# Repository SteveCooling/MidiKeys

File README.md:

# MidiKeys

Dissecting an old broken organ I got the idea to turn it into a MIDI keyboard.

I've since gotten a keybed that already had dual key switches for the velocity sensitivity, and been working on circuitry and code to support velocity sensitivity.

My plan is to produce a versatile open source keyboard controller board that can be used in various keyboard projects.

Works:

* Velocity sensitive multiplexed keyboard scanning
* Note off velocity sensitivity (not common in commercial keyboards, fun to be had here)

Plans:

* Work out the bugs in the keyboard scanner (keys sometimes hang or go undetected)
* Pot/slider (analog input) multiplexing
* Dedicated PCB with all required components and connectors
* Aftertouch support (channel pressure)
  * Maybe pseudo-polyphonic aftertouch is possible using a handful of pressure sensors (one per octave?) and interpolating the key pressure. Not sure about this.

Maybe in time:

* Mackie style DAW control support
* Keyboard splits and layers
* Interactive configuration from computer
* Arpeggiator with some cool touches?
  * Internal or MIDI timing
  * Oneshot/lick mode: Only arpeggiate when multiple keys are on, and in play order. Lay a chord and let the keyboard "slide" through the notes for you. In tempo.

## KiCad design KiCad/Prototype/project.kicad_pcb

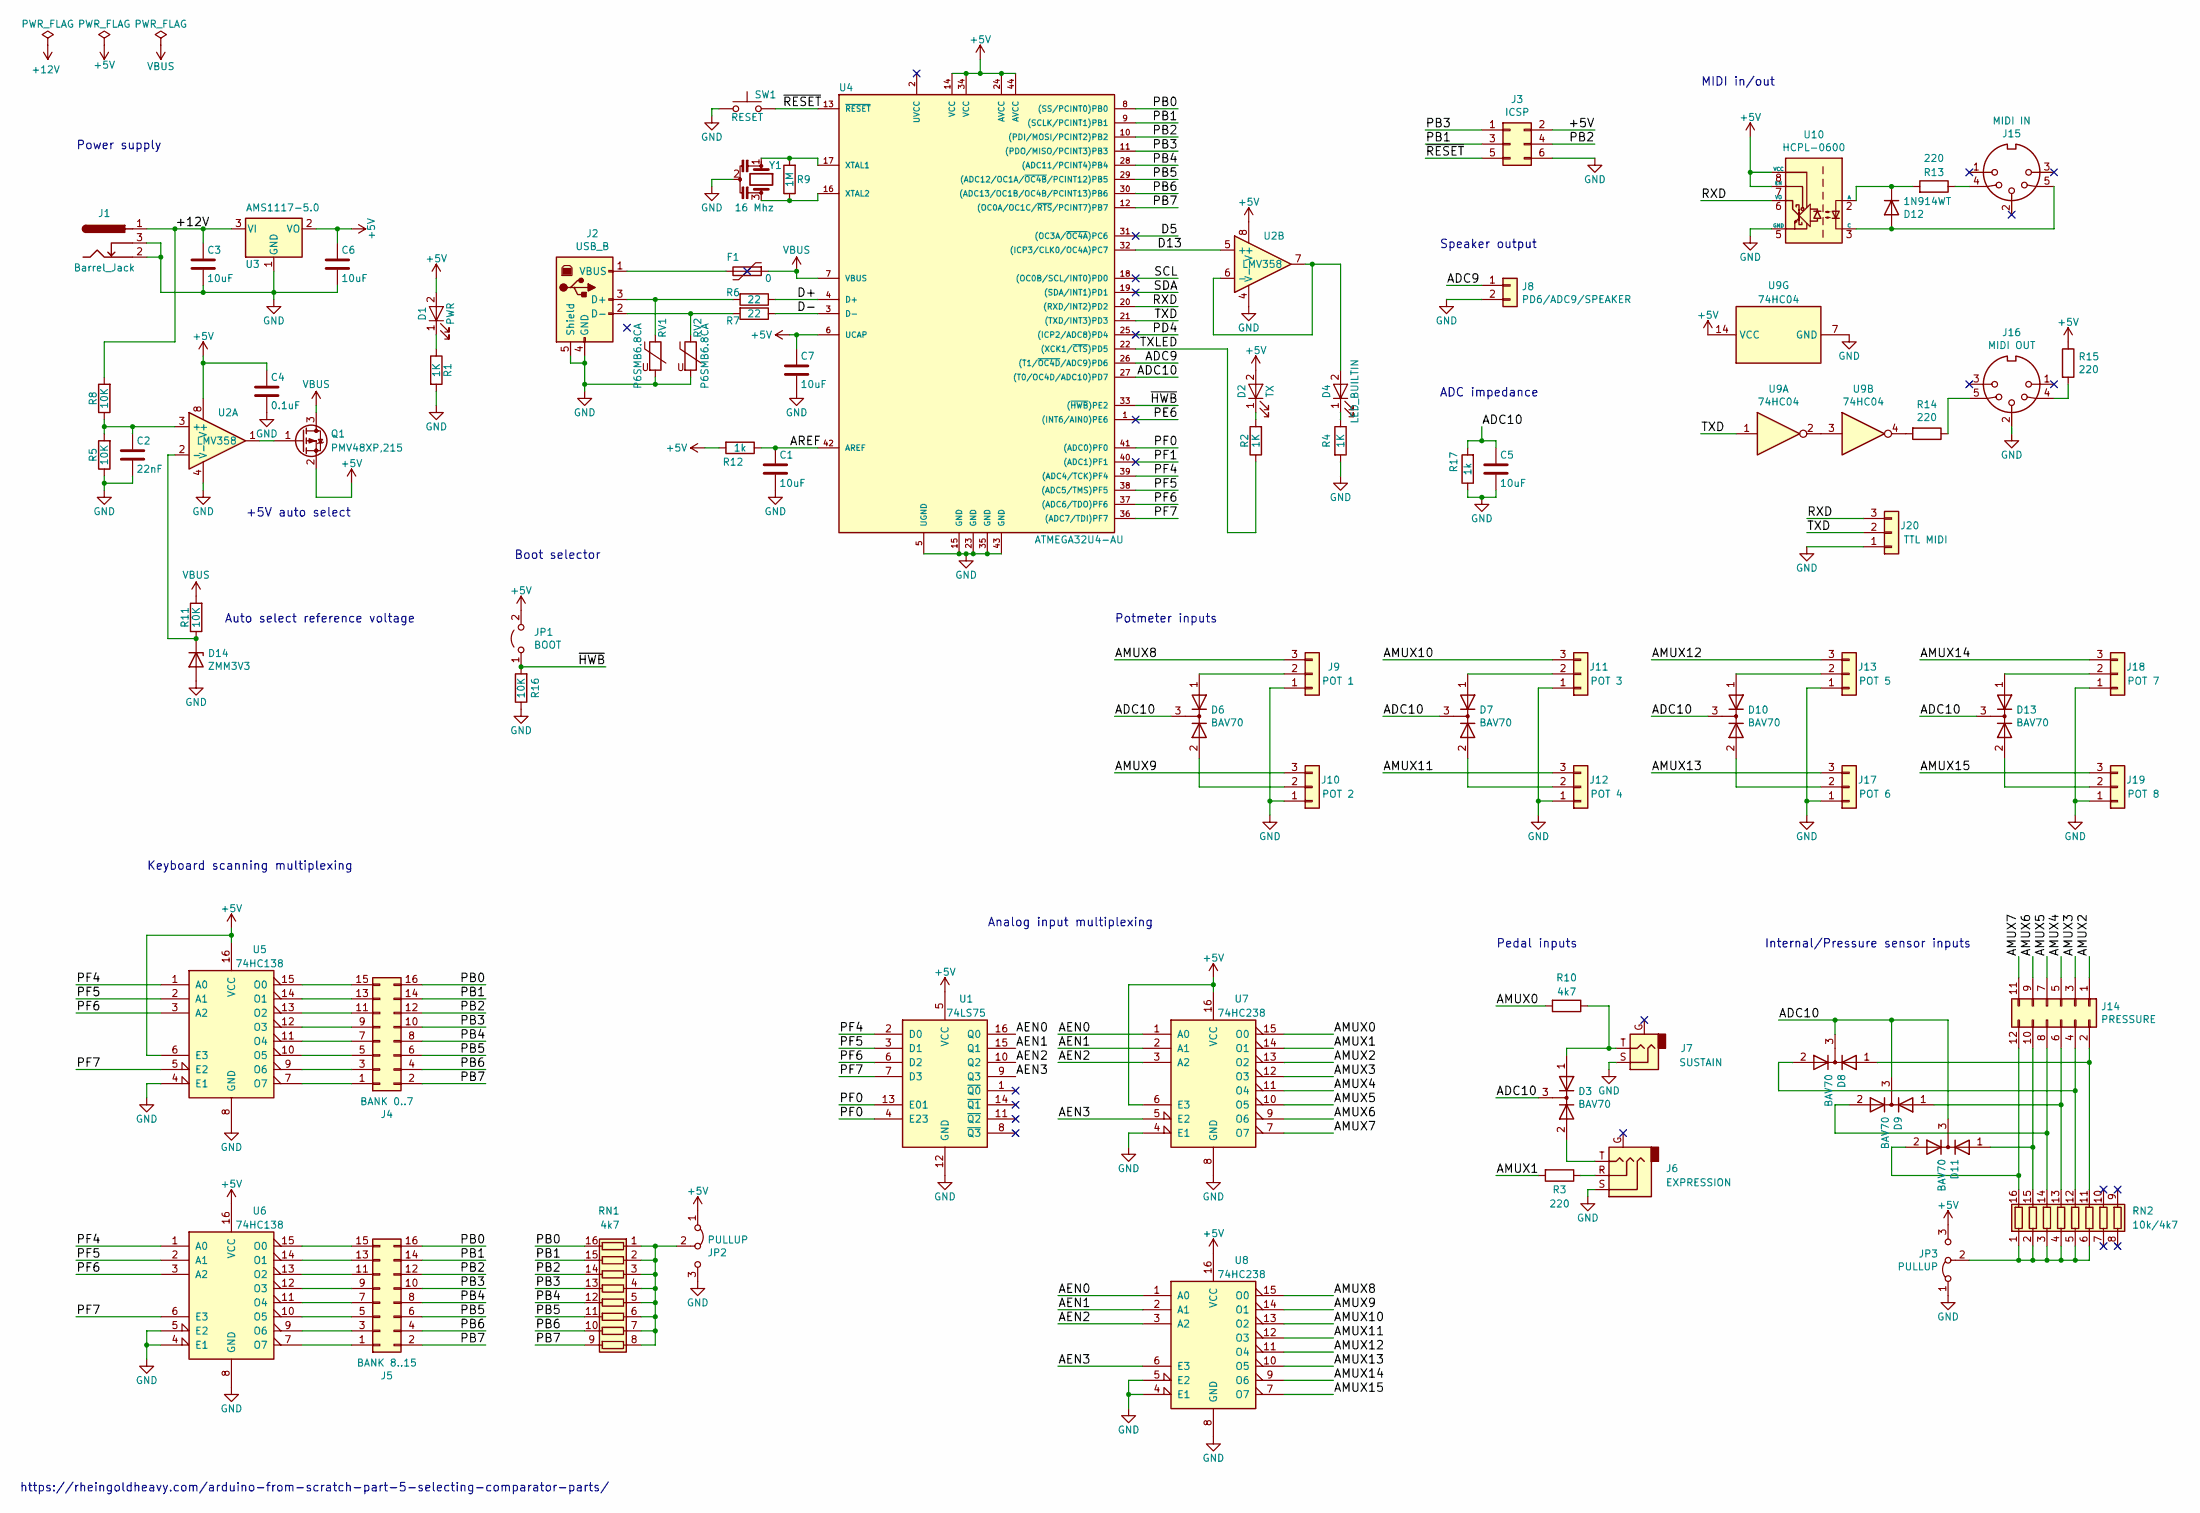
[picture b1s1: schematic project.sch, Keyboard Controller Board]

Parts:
C1, C3, C5, C6, C7: 10uF; C_1206_HandSoldering; LCSC C13585
C2: 22nF; C_0805_HandSoldering; LCSC C1729
C4: 0.1uF; C_0805_HandSoldering; LCSC C49678
D1: PWR; LED_0805_HandSoldering; LCSC C84256
D2: TX; LED_0805_HandSoldering; LCSC C84256
D3, D6, D7, D8, D9, D10, D11, D13: BAV70; SOT-23; LCSC C68978
D4: LED_BUILTIN; LED_0805_HandSoldering; LCSC C84256
D12: 1N914WT; D_SOD-323; LCSC C2128
D14: ZMM3V3; D_MiniMELF; LCSC C8056
F1: 0; R_1206_HandSoldering; LCSC C17888
J1: Barrel_Jack; BARREL_JACK; MOUSER 490-PJ-102A
J2: USB_B; USB_B_OST_USB-B1HSxx_Horizontal; MOUSER 490-UJ2-BH-1-TH
J3: ICSP; IDC-Header_2x03_P2.54mm_Vertical; MOUSER 517-30306-6002HB
J4: BANK 0..7; IDC-Header_2x08_P2.54mm_Vertical; MOUSER 517-30316-6002
J5: BANK 8..15; IDC-Header_2x08_P2.54mm_Vertical; MOUSER 517-30316-6002
J6: EXPRESSION; Jack_6.35mm_Amphenol_ACJS-MHDR; MOUSER 523-ACJS-MHOP
J7: SUSTAIN; Jack_6.35mm_Amphenol_ACJM-MHDR; MOUSER 523-ACJS-MHOP
J8: PD6/ADC9/SPEAKER; Molex_KK-254_AE-6410-02A_1x02_P2.54mm_Vertical; MOUSER 571-640454-2
J9: POT 1; Molex_KK-254_AE-6410-03A_1x03_P2.54mm_Vertical; MOUSER 571-6404543
J10: POT 2; Molex_KK-254_AE-6410-03A_1x03_P2.54mm_Vertical; MOUSER 571-6404543
J11: POT 3; Molex_KK-254_AE-6410-03A_1x03_P2.54mm_Vertical; MOUSER 571-6404543
J12: POT 4; Molex_KK-254_AE-6410-03A_1x03_P2.54mm_Vertical; MOUSER 571-6404543
J13: POT 5; Molex_KK-254_AE-6410-03A_1x03_P2.54mm_Vertical; MOUSER 571-6404543
J14: PRESSURE; IDC-Header_2x06_P2.54mm_Vertical
J15: MIDI IN; DIN_5_180Deg_PSG03463; MOUSER 806-KCDX-5S-N2
J16: MIDI OUT; DIN_5_180Deg_PSG03463; MOUSER 806-KCDX-5S-N2
J17: POT 6; Molex_KK-254_AE-6410-03A_1x03_P2.54mm_Vertical; MOUSER 571-6404543
J18: POT 7; Molex_KK-254_AE-6410-03A_1x03_P2.54mm_Vertical; MOUSER 571-6404543
J19: POT 8; Molex_KK-254_AE-6410-03A_1x03_P2.54mm_Vertical; MOUSER 571-6404543
J20: TTL MIDI; Molex_KK-254_AE-6410-03A_1x03_P2.54mm_Vertical; MOUSER 571-6404543
JP1: BOOT; SolderJumper-2_P1.3mm_Open_Pad1.0x1.5mm
JP2, JP3: PULLUP; SolderJumper-3_P1.3mm_Bridged12_Pad1.0x1.5mm
Q1: PMV48XP,215; SOT-23; LCSC C75560
R1, R2, R4: 1K; R_0805_HandSoldering; LCSC C17513
R3, R13, R14, R15: 220; C_0805_HandSoldering; LCSC C17557
R5, R8, R11, R16: 10K; R_0805_HandSoldering; LCSC C17414
R6, R7: 22; R_0805_HandSoldering; LCSC C17561
R9: 1M; R_0805_HandSoldering; LCSC C17514
R10: 4k7; C_0805_HandSoldering; LCSC C17673
R12, R17: 1k; R_0805_HandSoldering; LCSC C17561
RN1: 4k7; SOIC-16_4.55x10.3mm_P1.27mm
RN2: 10k/4k7; SOIC-16_4.55x10.3mm_P1.27mm
RV1, RV2: P6SMB6.8CA; D_SMB; LCSC C78395
SW1: RESET; SW_SPST_PTS645
U1: 74LS75; SOIC-16_4.55x10.3mm_P1.27mm
U2: LMV358; VSSOP-8_3.0x3.0mm_Pitch0.65mm
U3: AMS1117-5.0; SOT-223-3_TabPin2; LCSC C6187
U4: ATMEGA32U4-AU; TQFP-44_10x10mm_Pitch0.8mm; MOUSER 556-ATMEGA32U4-AU
U5, U6: 74HC138; SOIC-16_4.55x10.3mm_P1.27mm; MOUSER 771-74HC138D
U7, U8: 74HC238; SOIC-16_4.55x10.3mm_P1.27mm; MOUSER 771-74HC238D
U9: 74HC04; SOIC-14_3.9x8.7mm_P1.27mm
U10: HCPL-0600; SOIC-8_3.9x4.9mm_P1.27mm; MOUSER 512-HCPL0600
Y1: 16 Mhz; Resonator_SMD_CTSC_1.3mmx3.2mm

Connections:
+5V: C4.1, C6.1, C7.1, D1.2 (A), D2.2 (A), J3.2, JP1.2 (B), JP2.1 (A), JP3.3 (B), Q1.2 (S), R12.2, R15.1, U1.5 (VCC), U2.8 (V+), U3.2 (VO), U4.6 (UCAP), U4.14 (VCC), U4.24 (AVCC), U4.34 (VCC), U4.44 (AVCC), U5.6 (E3), U5.16 (VCC), U6.16 (VCC), U7.6 (E3), U7.16 (VCC), U8.16 (VCC), U9.14 (VCC), U10.7 (EN), U10.8 (VCC)
+12V: C3.1, J1.1, R8.2, U3.3 (VI)
/ADC9: J8.1, U4.26 ((T1/~OC4D~/ADC9)PD6)
/ADC10: C5.1, D3.3 (K), D6.3 (K), D7.3 (K), D8.3 (K), D9.3 (K), D10.3 (K), D11.3 (K), D13.3 (K), R17.2, U4.27 ((T0/OC4D/ADC10)PD7)
/AEN0: U1.16 (Q0), U7.1 (A0), U8.1 (A0)
/AEN1: U1.15 (Q1), U7.2 (A1), U8.2 (A1)
/AEN2: U1.10 (Q2), U7.3 (A2), U8.3 (A2)
/AEN3: U1.9 (Q3), U7.5 (E2), U8.6 (E3)
/AMUX0: R10.2, U7.15 (O0)
/AMUX1: R3.2, U7.14 (O1)
/AMUX2: J14.1, U7.13 (O2)
/AMUX3: J14.3, U7.12 (O3)
/AMUX4: J14.5, U7.11 (O4)
/AMUX5: J14.7, U7.10 (O5)
/AMUX6: J14.9, U7.9 (O6)
/AMUX7: J14.11, U7.7 (O7)
/AMUX8: J9.3, U8.15 (O0)
/AMUX9: J10.3, U8.14 (O1)
/AMUX10: J11.3, U8.13 (O2)
/AMUX11: J12.3, U8.12 (O3)
/AMUX12: J13.3, U8.11 (O4)
/AMUX13: J17.3, U8.10 (O5)
/AMUX14: J18.3, U8.9 (O6)
/AMUX15: J19.3, U8.7 (O7)
/AREF: C1.1, R12.1, U4.42 (AREF)
/D5: U4.31 ((OC3A/~OC4A~)PC6)
/D13: U2.5 (+), U4.32 ((ICP3/CLK0/OC4A)PC7)
/D+: R6.1, U4.4 (D+)
/D-: R7.1, U4.3 (D-)
/PB0: J4.16, J5.16, RN1.16 (R1.2), U4.8 ((SS/PCINT0)PB0)
/PB1: J3.3, J4.14, J5.14, RN1.15 (R2.2), U4.9 ((SCLK/PCINT1)PB1)
/PB2: J3.4, J4.12, J5.12, RN1.14 (R3.2), U4.10 ((PDI/MOSI/PCINT2)PB2)
/PB3: J3.1, J4.10, J5.10, RN1.13 (R4.2), U4.11 ((PDO/MISO/PCINT3)PB3)
/PB4: J4.8, J5.8, RN1.12 (R5.2), U4.28 ((ADC11/PCINT4)PB4)
/PB5: J4.6, J5.6, RN1.11 (R6.2), U4.29 ((ADC12/OC1A/~OC4B~/PCINT12)PB5)
/PB6: J4.4, J5.4, RN1.10 (R7.2), U4.30 ((ADC13/OC1B/OC4B/PCINT13)PB6)
/PB7: J4.2, J5.2, RN1.9 (R8.2), U4.12 ((OC0A/OC1C/~RTS~/PCINT7)PB7)
/PD4: U4.25 ((ICP2/ADC8)PD4)
/PE6: U4.1 ((INT6/AIN0)PE6)
/PF0: U1.4 (E23), U1.13 (E01), U4.41 ((ADC0)PF0)
/PF1: U4.40 ((ADC1)PF1)
/PF4: U1.2 (D0), U4.39 ((ADC4/TCK)PF4), U5.1 (A0), U6.1 (A0)
/PF5: U1.3 (D1), U4.38 ((ADC5/TMS)PF5), U5.2 (A1), U6.2 (A1)
/PF6: U1.6 (D2), U4.37 ((ADC6/TDO)PF6), U5.3 (A2), U6.3 (A2)
/PF7: U1.7 (D3), U4.36 ((ADC7/TDI)PF7), U5.5 (E2), U6.6 (E3)
/RXD: J20.3, U4.20 ((RXD/INT2)PD2), U10.6 (VO)
/SCL: U4.18 ((OC0B/SCL/INT0)PD0)
/SDA: U4.19 ((SDA/INT1)PD1)
/TXD: J20.2, U4.21 ((TXD/INT3)PD3), U9.1
/TXLED: R2.1, U4.22 ((XCK1/~CTS~)PD5)
/~HWB: JP1.1 (A), R16.2, U4.33 ((~HWB~)PE2)
/~RESET: J3.5, SW1.2, U4.13 (~RESET~)
GND: C1.2, C2.2, C3.2, C4.2, C5.2, C6.2, C7.2, D14.2 (A), J1.2, J1.3, J2.4 (GND), J2.5 (Shield), J3.6, J6.S, J7.S, J8.2, J9.1, J10.1, J11.1, J12.1, J13.1, J16.2, J17.1, J18.1, J19.1, J20.1, JP2.3 (B), JP3.1 (A), R1.2, R4.2, R5.1, R16.1, R17.1, RV1.2, RV2.2, SW1.1, U1.12 (GND), U2.4 (V-), U3.1 (GND), U4.5 (UGND), U4.15 (GND), U4.23 (GND), U4.35 (GND), U4.43 (GND), U5.4 (E1), U5.8 (GND), U6.4 (E1), U6.5 (E2), U6.8 (GND), U7.4 (E1), U7.8 (GND), U8.4 (E1), U8.5 (E2), U8.8 (GND), U9.7 (GND), U10.5 (GND), Y1.2
unnamed: C2.1, R5.2, R8.1, U2.3 (+)
unnamed: D1.1 (K), R1.1
unnamed: D2.1 (K), R2.2
unnamed: D3.1 (A), J7.T, R10.1
unnamed: D3.2 (A), J6.T
unnamed: D4.1 (K), R4.1
unnamed: D4.2 (A), U2.6 (-), U2.7
unnamed: D6.1 (A), J9.2
unnamed: D6.2 (A), J10.2
unnamed: D7.1 (A), J11.2
unnamed: D7.2 (A), J12.2
unnamed: D8.1 (A), J14.2, RN2.11 (R6.2)
unnamed: D8.2 (A), J14.4, RN2.12 (R5.2)
unnamed: D9.1 (A), J14.6, RN2.13 (R4.2)
unnamed: D9.2 (A), J14.8, RN2.14 (R3.2)
unnamed: D10.1 (A), J13.2
unnamed: D10.2 (A), J17.2
unnamed: D11.1 (A), J14.10, RN2.15 (R2.2)
unnamed: D11.2 (A), J14.12, RN2.16 (R1.2)
unnamed: D12.1 (K), R13.2, U10.2 (A)
unnamed: D12.2 (A), J15.5, U10.3 (C)
unnamed: D13.1 (A), J18.2
unnamed: D13.2 (A), J19.2
unnamed: D14.1 (K), R11.1, U2.2 (-)
unnamed: F1.2, J2.1 (VBUS)
unnamed: J2.2 (D-), R7.2, RV2.1
unnamed: J2.3 (D+), R6.2, RV1.1
unnamed: J4.1, U5.7 (O7)
unnamed: J4.3, U5.9 (O6)
unnamed: J4.5, U5.10 (O5)
unnamed: J4.7, U5.11 (O4)
unnamed: J4.9, U5.12 (O3)
unnamed: J4.11, U5.13 (O2)
unnamed: J4.13, U5.14 (O1)
unnamed: J4.15, U5.15 (O0)
unnamed: J5.1, U6.7 (O7)
unnamed: J5.3, U6.9 (O6)
unnamed: J5.5, U6.10 (O5)
unnamed: J5.7, U6.11 (O4)
unnamed: J5.9, U6.12 (O3)
unnamed: J5.11, U6.13 (O2)
unnamed: J5.13, U6.14 (O1)
unnamed: J5.15, U6.15 (O0)
unnamed: J6.R, R3.1
unnamed: J15.4, R13.1
unnamed: J16.4, R15.2
unnamed: J16.5, R14.1
unnamed: JP2.2 (C), RN1.1 (R1.1), RN1.2 (R2.1), RN1.3 (R3.1), RN1.4 (R4.1), RN1.5 (R5.1), RN1.6 (R6.1), RN1.7 (R7.1), RN1.8 (R8.1)
unnamed: JP3.2 (C), RN2.1 (R1.1), RN2.2 (R2.1), RN2.3 (R3.1), RN2.4 (R4.1), RN2.5 (R5.1), RN2.6 (R6.1)
unnamed: Q1.1 (G), U2.1
unnamed: R9.1, U4.16 (XTAL2), Y1.3
unnamed: R9.2, U4.17 (XTAL1), Y1.1
unnamed: R14.2, U9.4
unnamed: U9.2, U9.3
VBUS: F1.1, Q1.3 (D), R11.2, U4.7 (VBUS)

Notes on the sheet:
https://rheingoldheavy.com/arduino-from-scratch-part-5-selecting-comparator-parts/
Keyboard scanning multiplexing
Analog input multiplexing
Potmeter inputs
Pedal inputs
Internal/Pressure sensor inputs
MIDI in/out
Speaker output
Power supply
Boot selector
+5V auto select
Auto select reference voltage
ADC impedance

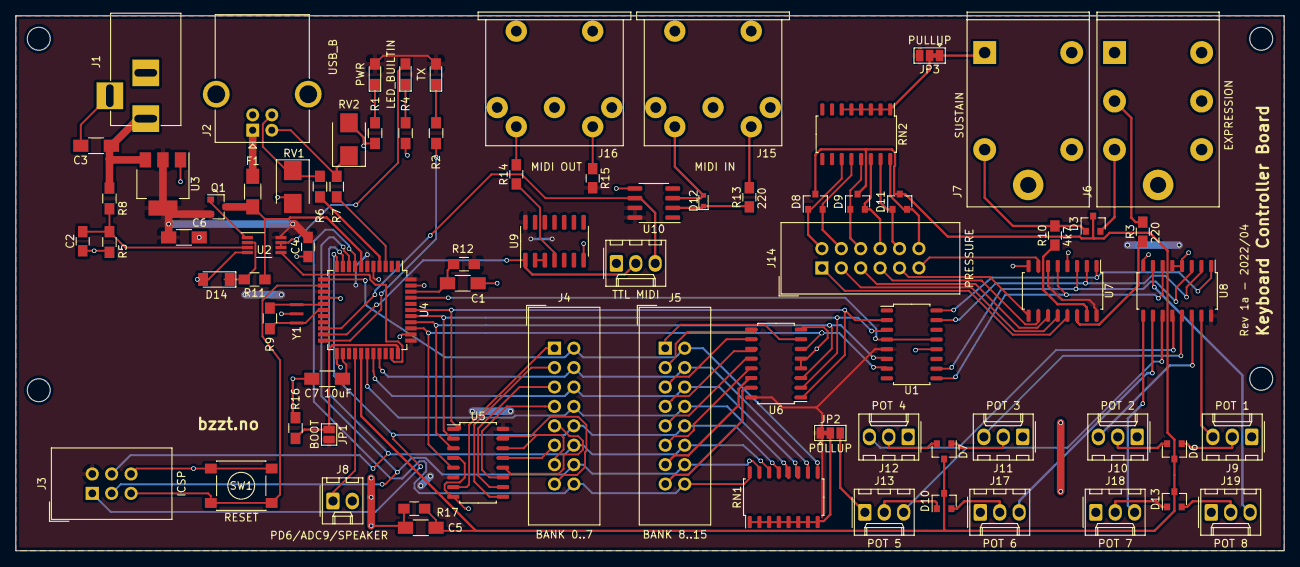
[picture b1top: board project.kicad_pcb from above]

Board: 2 copper layers, 166.0 x 70.0 mm, 78 parts (0 on the bottom side), 102 nets.

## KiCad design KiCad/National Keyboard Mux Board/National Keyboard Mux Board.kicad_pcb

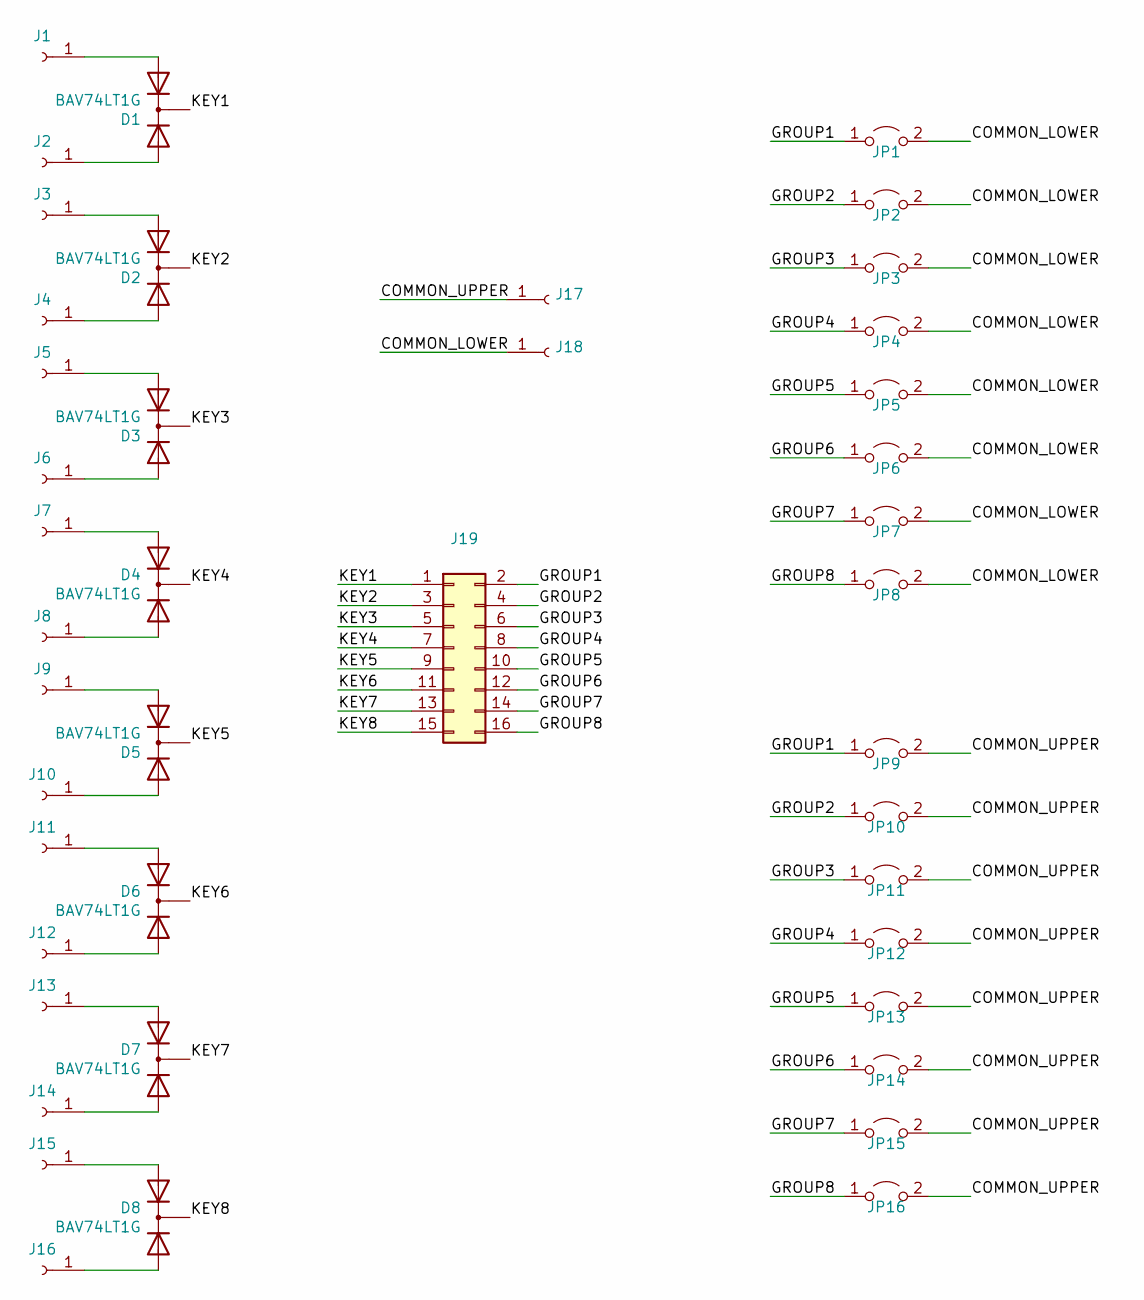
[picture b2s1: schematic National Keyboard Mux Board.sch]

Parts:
D1, D2, D3, D4, D5, D6, D7, D8: BAV74LT1G; SOT-23; LCSC C82481
J1, J2, J3, J4, J5, J6, J7, J8, J9, J10, J11, J12, J13, J14, J15, J16, J17, J18: Conn_01x01_Female; PinSlot_1x3.5mm_Flat
J19: Conn_02x08_Odd_Even; IDC-Header_2x08_P2.54mm_Vertical; LCSC C492443
JP1, JP2, JP3, JP4, JP5, JP6, JP7, JP8, JP9, JP10, JP11, JP12, JP13, JP14, JP15, JP16: Jumper_2_Open; SolderJumper-2_P1.3mm_Open_Pad1.0x1.5mm

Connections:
/COMMON_LOWER: J18.1, JP1.2 (B), JP2.2 (B), JP3.2 (B), JP4.2 (B), JP5.2 (B), JP6.2 (B), JP7.2 (B), JP8.2 (B)
/COMMON_UPPER: J17.1, JP9.2 (B), JP10.2 (B), JP11.2 (B), JP12.2 (B), JP13.2 (B), JP14.2 (B), JP15.2 (B), JP16.2 (B)
/GROUP1: J19.2, JP1.1 (A), JP9.1 (A)
/GROUP2: J19.4, JP2.1 (A), JP10.1 (A)
/GROUP3: J19.6, JP3.1 (A), JP11.1 (A)
/GROUP4: J19.8, JP4.1 (A), JP12.1 (A)
/GROUP5: J19.10, JP5.1 (A), JP13.1 (A)
/GROUP6: J19.12, JP6.1 (A), JP14.1 (A)
/GROUP7: J19.14, JP7.1 (A), JP15.1 (A)
/GROUP8: J19.16, JP8.1 (A), JP16.1 (A)
/KEY1: D1.3 (CATHODE), J19.1
/KEY2: D2.3 (CATHODE), J19.3
/KEY3: D3.3 (CATHODE), J19.5
/KEY4: D4.3 (CATHODE), J19.7
/KEY5: D5.3 (CATHODE), J19.9
/KEY6: D6.3 (CATHODE), J19.11
/KEY7: D7.3 (CATHODE), J19.13
/KEY8: D8.3 (CATHODE), J19.15
unnamed: D1.1 (ANODE_1), J1.1
unnamed: D1.2 (ANODE_2), J2.1
unnamed: D2.1 (ANODE_1), J3.1
unnamed: D2.2 (ANODE_2), J4.1
unnamed: D3.1 (ANODE_1), J5.1
unnamed: D3.2 (ANODE_2), J6.1
unnamed: D4.1 (ANODE_1), J8.1
unnamed: D4.2 (ANODE_2), J7.1
unnamed: D5.1 (ANODE_1), J9.1
unnamed: D5.2 (ANODE_2), J10.1
unnamed: D6.1 (ANODE_1), J12.1
unnamed: D6.2 (ANODE_2), J11.1
unnamed: D7.1 (ANODE_1), J14.1
unnamed: D7.2 (ANODE_2), J13.1
unnamed: D8.1 (ANODE_1), J16.1
unnamed: D8.2 (ANODE_2), J15.1

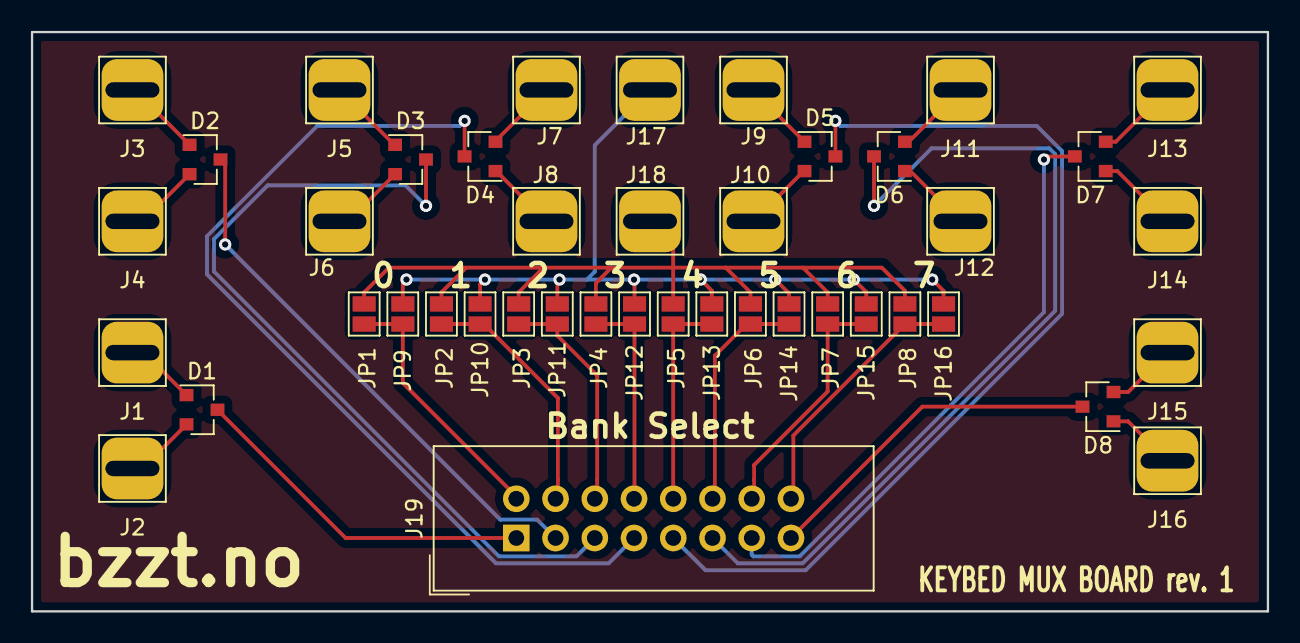
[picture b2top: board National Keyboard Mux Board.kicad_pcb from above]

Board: 2 copper layers, 80.0 x 37.5 mm, 43 parts (0 on the bottom side), 34 nets.

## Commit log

2020-04-02 vscode
2020-04-04 moved code to make room for other parts of the project
2020-04-04 also move vscode settings
2020-04-04 Work on velocity sensitivity
2020-04-04 started on PCB
2020-04-04 KiCad schematics
2020-04-05 deleted an oops
2020-04-05 mainly finished schematic
2020-04-05 more footprints
2020-04-07 more work on schematic, started layout
2020-04-11 more routing
2020-04-17 housekeeping
2020-04-17 Way less note hangs. Speed optimizations.
2020-05-05 cleanups and work on #1
2020-05-06 Create LICENSE
2020-10-17 vscode config
2021-05-06 committing older misc changes
2021-05-06 Include keybed mux bus PCB
2021-05-06 more settings
2021-05-06 Swithed to dual SMT diodes and made schematic prettier
2021-05-08 production files
2021-05-10 Removed unneccessary 3V3 regulator Added latch for ADC multiplexing
2021-05-11 Readying schematic and routing for prototype production
2021-06-03 more work towards production
2021-10-19 minor tweaks
2022-01-17 missing connection. silkscreen adjustments.
2022-01-23 Migrated firmware to PlatformIO
2022-01-24 cleanup
2022-01-24 Fix Kibot problems
2022-01-24 trying again
2022-01-24 Silkscreen Logo added
2022-01-24 PCB photo
2022-02-17 bootloader and fuse settings
2022-02-17 bringup of new board.
2022-02-17 working pc speaker synth
2022-02-17 more synth stuff
2022-05-02 first concept of bank latching
2022-05-02 banking works now
2022-05-03 mux reading works
2022-05-08 electrical changes for analog mux
